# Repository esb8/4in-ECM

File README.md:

# Media

---

<div align="center">
  <div>

    <p><em>3D Render</em></p>
  </div>
  <br>

  <div>
    <br>
    <p><em>Schematic</em></p>
  </div>
  <br>
  
  <div>
    
    <br>
    <em>Footprint</em>
  </div>
</div>

# Engine Control Module

## Overview  
The **Engine Control Module (ECM)** is a **control and data acquisition (DAQ) system** designed for liquid rocket engine testing. It integrates sensor measurement, actuation control, and data logging into a compact embedded system suitable for ground testing and development.  

The system is capable of:  
- Monitoring **up to 4 pressure transducers**  
- Reading multiple **thermocouples** for temperature measurement  
- Controlling **1 solenoid valve** (on/off flow control)  
- Driving **2 servo motors** (valve actuation or gimbal control)  
- Logging sensor data for analysis and verification  

---

## Features  
- **Data Acquisition**  
  - 4 analog channels for high-accuracy pressure transducers  
  - Integrated thermocouple interface for combustion chamber and feed line monitoring  
  - Real-time sampling and logging  

- **Actuation**  
  - Solenoid driver with high-side switching capability  
  - Dual servo motor outputs (PWM control)  
  - Configurable control logic for sequencing and automation  

- **System Control**  
  - Embedded microcontroller (e.g., STM32/Arduino/FPGA – specify)  
  - USB/UART interface for PC communication  
  - Safety interlocks and emergency shutdown support  

- **Software**  
  - Firmware for DAQ, control, and communications  
  - Logging utility for test data collection  
  - Configurable sampling rates and actuation sequences  

---

## Applications  
- Small-scale **liquid rocket engine testing**  
- **Valve and feed system automation**  
- **Sensor data acquisition** for propulsion research  
- **Ground support equipment** integration  

---

## Getting Started  
1. **Hardware Setup**  
   - Connect pressure transducers to the analog input ports (0–5 V or 0–10 V).  
   - Connect thermocouples to the thermocouple inputs.  
   - Wire solenoid to the high-side driver output.  
   - Connect servos to PWM headers.  

2. **Software Setup**  
   - Flash firmware using the provided source code.  
   - Install the DAQ/logging software on your PC.  
   - Configure serial port and sampling rate.  

3. **Operation**  
   - Power on the ECM.  
   - Verify sensor calibration.  
   - Execute control sequences via PC interface or onboard logic.  

---

## Safety Notes  
⚠️ This module is intended for **research and experimental use only**.  
- Always follow proper test stand safety procedures.  
- Use protective enclosures and remote operation where possible.  
- Ensure solenoid and servo actuation logic is validated before hot-fire testing.

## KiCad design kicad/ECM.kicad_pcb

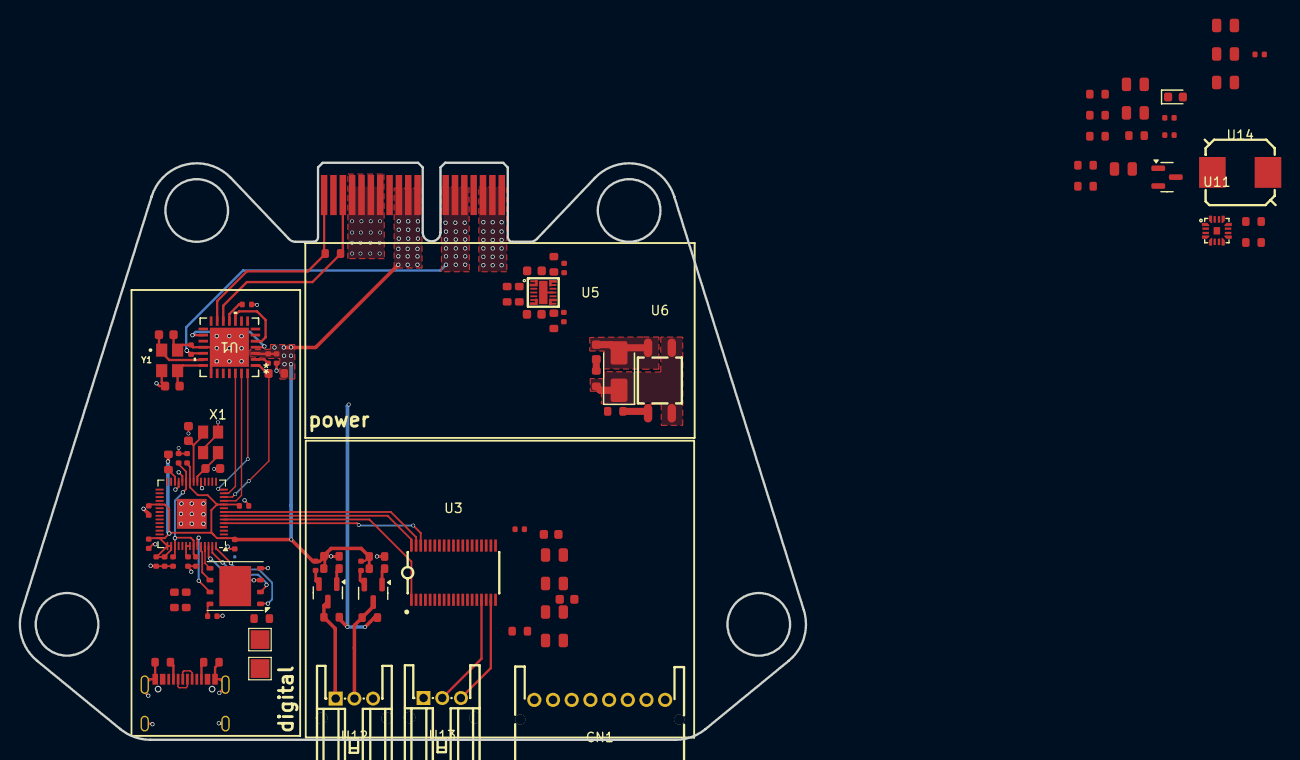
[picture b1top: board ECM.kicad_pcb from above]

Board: 4 copper layers, 84.1 x 61.7 mm, 92 parts (1 on the bottom side), 66 nets.

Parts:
C1, C2, C4, C5, C6, C7, C8, C9, C10, C14, C15, C16, C17, C29, C30, C37: 100nF; C_0402
C3, C11, C23: 1uF; C_0402
C12, C13: 15pF; C_0603
C18, C21, C24, C28: 1uF; C_0603
C19, C20: 22pF; C_0603
C22, C25, C26, C27, C38, C39, C40, C41, C42: 10uF; C_0805
C31: 22nF; C_0603
C36: 2.2uF; C_0805
C43: 220pF; C_0402
CN1: S08B-PASK-2(LF)(SN); CONN-TH_S08B-PASK-2
D1: SS210; D_SMA
D2: White; D_0603
J1: Bus_PCI_Express_x1; BUS_PCIexpress_x1
J6: USB_C_Receptacle_USB2.0_16P; USB_C_Receptacle_Palconn_UTC16-G
Q1, Q2, Q3: AO3400A; Q_SOT-23
R1, R4, R37: 1kΩ; R_0603
R2, R3, R8: 27Ω; R_0603
R5, R6, R10, R11, R12, R13, R16, R17, R19, R20, R32, R34: 5.1kΩ; R_0603
R7: 300Ω; R_0603
R9, R15, R18, R33, R35: 120Ω; R_0603
R14, R21: 10Ω; R_0603
R22, R23, R24, R29: 10kΩ; R_0402
R30, R36: 160kΩ; R_0603
R31: 22kΩ; R_0603
U1: MCP25625T-E/ML; QFN28_6X6MC_MCH
U2: RP2040; QFN-56-1EP_7x7mm_P0.4mm_EP3.2x3.2mm
U3: ADS8688IDBTR; TSSOP-38_L9.7-W4.4-P0.50-LS6.4-BL
U4: W25Q128JVP; WSON-8-1EP_6x5mm_P1.27mm_EP3.4x4.3mm
U5: TPS22976DPUR; WSON-14_L3.0-W2.0-P0.40-BL-EP-1
U6: GAQY252G3S; SOP-4_L4.3-W4.4-P2.54-LS7.0-BL
U11: SY8388ARHC; QFN-16_L2.5-W2.5-P0.45-TL-EP0.6
U12, U13: S03B-PASK-2; CONN-TH_S03B-PASK-2-LF-SN
U14: SPM7054VT-4R7M-D; IND-SMD_L7.5-W7.0_SPM7054VT-330M-D
X1: ABM8-272-T3; ABM8-272-T3_ABR
Y1: X322516MLB4SI; OSC_X322516MLB4SI

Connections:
+1V1: C1.1, C2.1, C3.1, U2.23 (DVDD), U2.45 (VREG_VOUT), U2.50 (DVDD)
+3.3V: C4.1, C5.1, C6.1, C7.1, C8.1, C9.1, C10.1, C11.1, C14.2, C15.2, C17.2, C25.1, J1.A9 (+3.3V), J1.A10 (+3.3V), J1.A11 (~PERST), J1.B9 (JTAG1), J1.B10 (3.3Vaux), J1.B11 (~WAKE), R4.2, R7.1, R10.1, R11.1, R15.1, R16.2, R17.2, R18.1, R22.2, R23.2, R24.2, U1.3 (VDD), U1.11 (VIO), U2.1 (IOVDD), U2.10 (IOVDD), U2.22 (IOVDD), U2.33 (IOVDD), U2.42 (IOVDD), U2.43 (ADC_AVDD), U2.44 (VREG_IN), U2.48 (USB_VDD), U2.49 (IOVDD), U3.34 (DVDD), U4.8 (VCC)
+5V: C16.1, C23.2, C24.1, J1.A12 (GND), J1.A13 (REFCLK+), J1.A14 (REFCLK-), J1.B12 (RSVD), J1.B13 (GND), J1.B14 (PETp0), U1.19 (VDDA), U3.9 (AVDD), U3.30 (AVDD)
+5V_Servo: C21.1, C28.1, C40.1, C41.1, C42.1, C43.1, R19.2, R20.2, R30.1, R33.1, R34.2, U5.1 (VIN1), U5.2 (VIN1), U5.4 (VBIAS), U5.6 (VIN2), U5.7 (VIN2), U14.1
+24V: C31.1, C38.2, C39.1, D1.2, R36.2, U6.4, U11.2 (IN), U11.3 (IN), U11.4 (IN), U12.3
+BAT: J1.A16 (PERp0), J1.A17 (PERn0), J1.A18 (GND), J1.B16 (GND), J1.B17 (~PRSNT2), J1.B18 (GND)
/3.3V_PWM1: Q1.2 (S), R22.1
/3.3V_PWM2: Q2.2 (S), R23.1
/5V_PWM1: Q1.3 (D), R20.1, U12.2
/5V_PWM2: Q2.3 (D), R19.1, U12.1
/AIN_0IN: U3.16 (AIN_0P), U13.2
/AIN_1IN: U3.18 (AIN_1P), U13.3
/CANH: J1.A1 (~PRSNT1), R9.2, U1.13 (CANH)
/CANL: J1.A3 (+12V), R9.1, U1.12 (CANL)
/CAN_OSC1: C19.1, U1.21 (OSC1), Y1.3
/CAN_OSC2: C20.1, U1.20 (OSC2), Y1.1
/FB: R30.2, R31.1, R37.2, U11.11 (FB)
/LX: C37.1, U11.5 (LX), U11.15 (LX), U11.16 (LX), U14.2
/MODE: R32.2, U11.8 (MODE)
/QSPI_SCLK: U2.52 (QSPI_SCLK), U4.6 (CLK)
/QSPI_SD0: U2.53 (QSPI_SD0), U4.5 (DI(IO0))
/QSPI_SD1: U2.55 (QSPI_SD1), U4.2 (DO(IO1))
/QSPI_SD2: U2.54 (QSPI_SD2), U4.3 (IO2)
/QSPI_SD3: U2.51 (QSPI_SD3), U4.7 (IO3)
/QSPI_SS: R1.2, U2.56 (QSPI_SS), U4.1 (~CS)
/REFCAP: C18.1, C22.1, C27.2, U3.7 (REFCAP)
/REFGND: C18.2, C22.2, C27.1, U3.6 (REFGND)
/REFIO: C26.2, U3.5 (REFIO)
/RXCAN: U1.5 (RXCAN), U1.10 (RXD)
/SERVO_ON1: R13.2, U5.3 (ON1)
/SERVO_ON2: R12.2, U5.5 (ON2)
/SERVO_PWR1: C29.1, CN1.7, R14.1, U5.13 (VOUT1), U5.14 (VOUT1)
/SERVO_PWR2: C30.1, CN1.8, R21.1, U5.8 (VOUT2), U5.9 (VOUT2)
/SPI0_CS0: R10.2, U2.3 (GPIO1), U2.7 (GPIO5), U2.28 (GPIO17), U2.32 (GPIO21), U3.38 (~CS)
/SPI0_MISO: U2.5 (GPIO3), U2.9 (GPIO7), U2.30 (GPIO19), U2.35 (GPIO23), U3.36 (SDO)
/SPI0_MOSI: U2.2 (GPIO0), U2.6 (GPIO4), U2.27 (GPIO16), U2.31 (GPIO20), U3.1 (SDI)
/SPI0_SCK: U2.4 (GPIO2), U2.8 (GPIO6), U2.29 (GPIO18), U2.34 (GPIO22), U3.37 (SCLK)
/SPI1_CS0: R11.2, U1.1 (*CS), U2.12 (GPIO9), U2.16 (GPIO13), U2.37 (GPIO25)
/SPI1_MISO: U1.28 (SO), U2.14 (GPIO11), U2.18 (GPIO15)
/SPI1_MOSI: U1.27 (SI), U2.11 (GPIO8), U2.15 (GPIO12), U2.36 (GPIO24)
/SPI1_SCK: U1.26 (SCK), U2.13 (GPIO10), U2.17 (GPIO14)
/TXCAN: U1.4 (TXCAN), U1.16 (TXD)
/USB_DM: J6.A7 (D-), J6.B7 (D-)
/USB_DN: J6.A6 (D+), J6.B6 (D+), R3.2
/XIN: C13.1, U2.20 (XIN), X1.3
/XOUT: C12.1, U2.21 (XOUT), X1.1
GND: C1.2, C2.2, C3.2, C4.2, C5.2, C6.2, C7.2, C8.2, C9.2, C10.2, C11.2, C12.2, C13.2, C14.1, C15.1, C16.2, C17.1, C19.2, C20.2, C21.2, C23.1, C24.2, C25.2, C26.1, C28.2, C29.2, C30.2, C36.2, C38.1, C39.2, C40.2, C41.2, C42.2, CN1.1, CN1.2, CN1.3, D1.1, D2.1, J1.A4 (GND), J1.A5 (JTAG2), J1.A6 (JTAG3), J1.A7 (JTAG4), J1.B1 (+12V), J1.B2 (+12V), J1.B3 (+12V), J1.B4 (GND), J1.B5 (SMCLK), J1.B6 (SMDAT), J1.B7 (GND), J6.A1 (GND), J6.A12 (GND), J6.B1 (GND), J6.B12 (GND), J6.S1 (SHIELD), R5.2, R6.2, R8.2, R12.1, R13.1, R14.2, R16.1, R17.1, R21.2, R29.1, R31.2, U1.18 (VSS), U1.22 (GND), U1.29 (EPAD), U2.19 (TESTEN), U2.57 (GND), U3.3 (DAISY), U3.4 (~REFSEL), U3.8 (AGND), U3.28 (AGND), U3.29 (AGND), U3.31 (AGND), U3.32 (AGND), U3.33 (DGND), U4.4 (GND), U5.11 (GND), U5.15 (EP), U6.2, U6.3, U11.6 (GND), U11.14 (GND), U11.17 (GND), U13.1, X1.2, X1.4, Y1.2, Y1.4
unnamed: C31.2, R8.1
unnamed: C43.2, R37.1
unnamed: J6.A5 (CC1), R5.1
unnamed: J6.B5 (CC2), R6.1
unnamed: Q1.1 (G), R15.2
unnamed: Q2.1 (G), R18.2
unnamed: Q3.3 (D), R35.2
unnamed: Q3.1 (G), R34.1, U11.7 (PG)
unnamed: D2.2, Q3.2 (S)
unnamed: R7.2, U6.1
unnamed: R33.2, R35.1
unnamed: R4.1, U2.26 (RUN)
unnamed: R24.1, U1.2 (*RESET)
unnamed: R3.1, U2.46 (USB_DM)
unnamed: R2.2, U2.47 (USB_DP)
unnamed: C37.2, U11.1 (BS)
unnamed: R36.1, U11.9 (EN)
unnamed: R29.2, U11.10 (ILMT)
unnamed: C36.1, U11.13 (VCC)

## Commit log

2025-09-07 First Commit: Added MCU, DAQ IC, and a few connectors
2025-09-07 Cleaned out old ECM pro file
2025-09-10 followed MACH Template
2025-09-11 Schematic Capture of RP2040, CAN Network, USB-C, Memory, DAQ, Servo Drivers and PWM Level Shifter.
2025-09-11 Update images
2025-09-12 Added control circuitry for Servos, PWM Level Shifting, and Solenoid Driving, Next Steps: Thermocouples and CJC
2025-09-13 Added thermocouple ICs and dc/dc circuitry for servo power
2025-09-14 Preliminary PCB Layout on most ICs, carved out analog, power and digital regions.
2025-09-14 More progress on layout
2025-09-16 feat: added latching connectors
